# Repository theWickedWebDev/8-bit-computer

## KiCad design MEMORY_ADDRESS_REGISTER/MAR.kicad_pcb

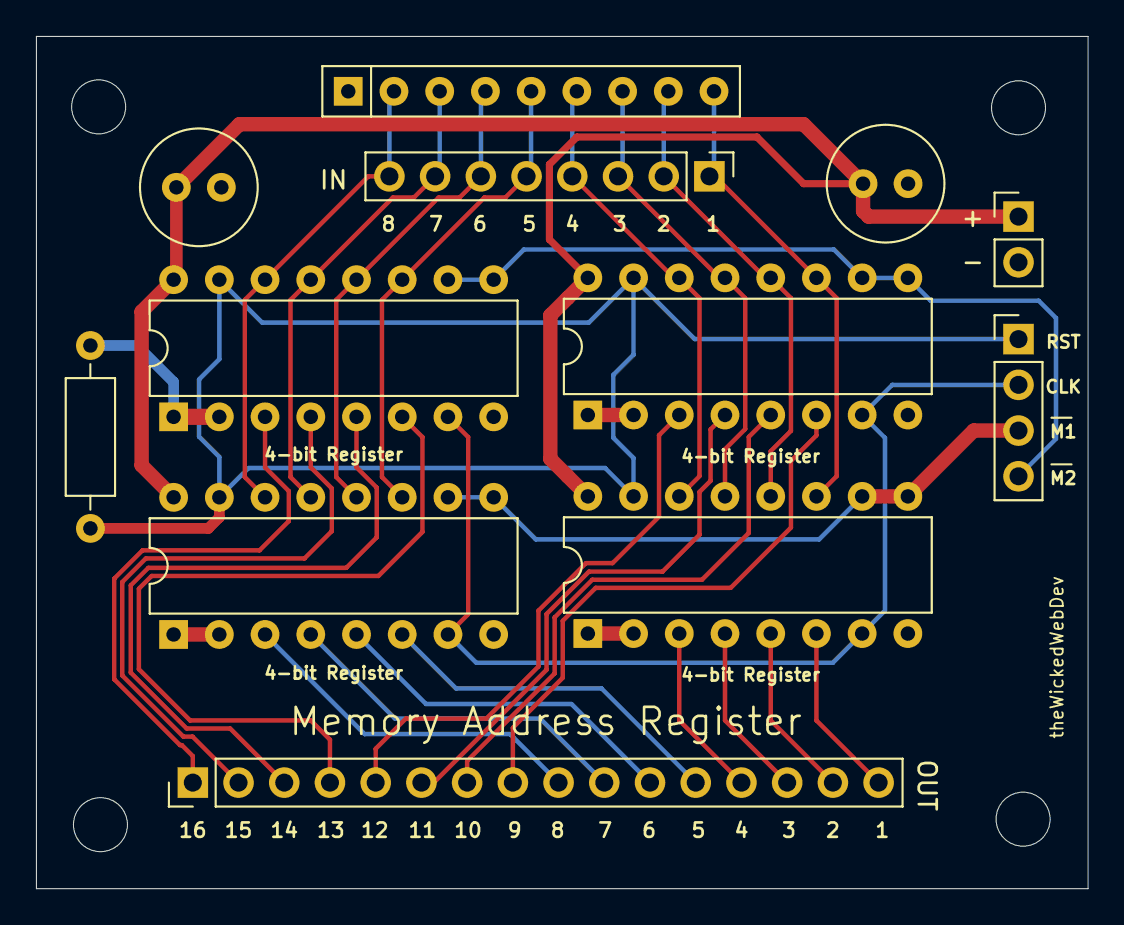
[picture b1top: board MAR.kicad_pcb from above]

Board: 2 copper layers, 58.4 x 47.3 mm, 12 parts (0 on the bottom side), 30 nets.

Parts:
C1, C2: CP1; C_Radial_D6.3mm_H11.0mm_P2.50mm
J1: Conn_01x04; PinHeader_1x02_P2.54mm_Vertical
J2: Conn_01x04; PinHeader_1x04_P2.54mm_Vertical
J3: Conn_01x08; PinHeader_1x08_P2.54mm_Vertical
J4: Conn_01x16; PinHeader_1x16_P2.54mm_Vertical
R1: R_Small_US; R_Axial_DIN0207_L6.3mm_D2.5mm_P10.16mm_Horizontal
RN1: R_Network08_US; R_Array_SIP9
U1, U2, U3, U4: 74LS173; DIP-16_W7.62mm

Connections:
/CLOCK: J2.2, U1.7, U2.7, U3.7, U4.7
/D1: J3.1, RN1.9, U3.11, U4.11
/D2: J3.2, RN1.8, U3.12, U4.12
/D3: J3.3, RN1.7, U3.13, U4.13
/D4: J3.4, RN1.6, U3.14, U4.14
/D5: J3.5, RN1.5, U1.11, U2.11
/D6: J3.6, RN1.4, U1.12, U2.12
/D7: J3.7, RN1.3, U1.13, U2.13
/D8: J3.8, RN1.2, U1.14, U2.14
/MAR1_IN: J2.3, U1.9, U1.10, U3.9, U3.10
/MAR2_IN: J2.4, U2.9, U2.10, U4.9, U4.10
/RESET: J2.1, R1.1, U1.15, U2.15, U3.15, U4.15
/Y1: J4.16, U3.6
/Y2: J4.15, U3.5
/Y3: J4.14, U3.4
/Y4: J4.13, U3.3
/Y5: J4.12, U1.6
/Y6: J4.11, U1.5
/Y7: J4.10, U1.4
/Y8: J4.9, U1.3
/Y9: J4.8, U4.6
/Y10: J4.7, U4.5
/Y11: J4.6, U4.4
/Y12: J4.5, U4.3
/Y13: J4.4, U2.6
/Y14: J4.3, U2.5
/Y15: J4.2, U2.4
/Y16: J4.1, U2.3
GND: C1.2, C2.2, J1.2, R1.2, RN1.1, U1.1, U1.2, U1.8, U2.1, U2.2, U2.8, U3.1, U3.2, U3.8, U4.1, U4.2, U4.8
VCC: C1.1, C2.1, J1.1, U1.16, U2.16, U3.16, U4.16

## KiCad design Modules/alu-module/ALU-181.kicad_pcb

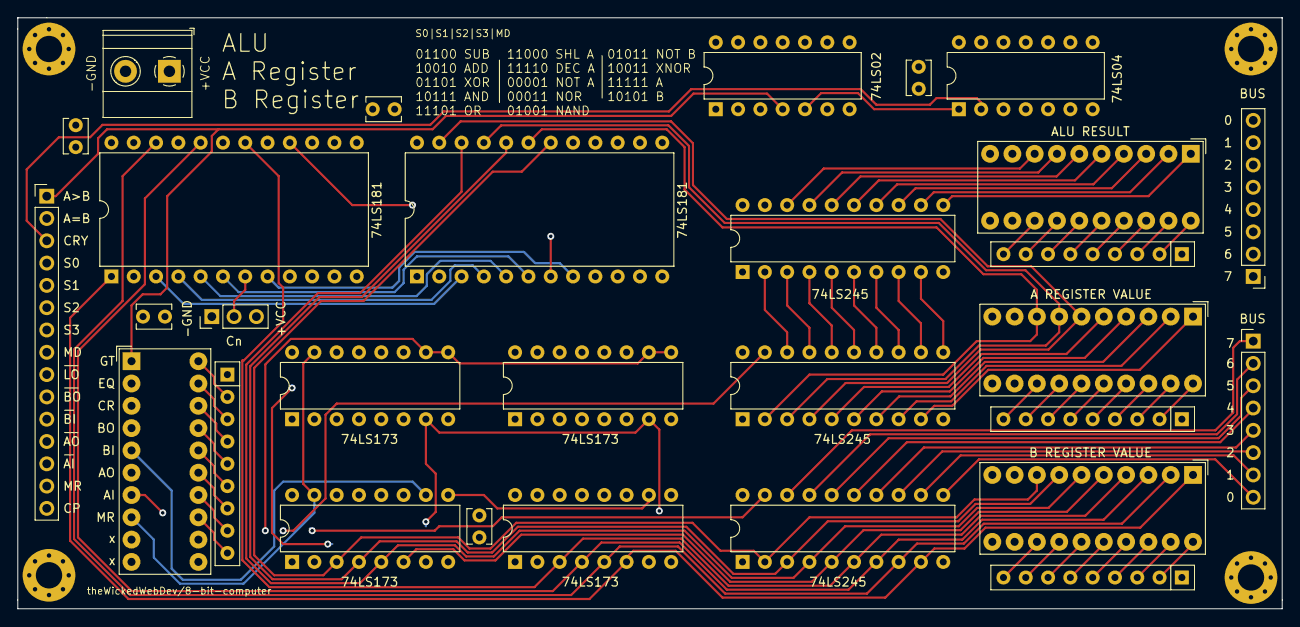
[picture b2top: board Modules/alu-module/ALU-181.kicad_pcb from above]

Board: 4 copper layers, 144.0 x 67.3 mm, 29 parts (0 on the bottom side), 85 nets.

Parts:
BAR1, BAR2, BAR3, BAR4: HDSP-4830_2; HDSP-4830
C1, C2, C3, C4, C5: CP1; C_Disc_D3.8mm_W2.6mm_P2.50mm
J1, J4: Conn_01x08; PinHeader_1x08_P2.54mm_Vertical
J2: Conn_01x15; PinHeader_1x15_P2.54mm_Vertical
J3: Screw_Terminal_01x02; TerminalBlock_Phoenix_MKDS-1,5-2_1x02_P5.00mm_Horizontal
J17: Conn_01x03; PinHeader_1x03_P2.54mm_Vertical
RN1, RN2, RN3, RN4: R_Network08; R_Array_SIP9
U1, U2, U10: 74LS245; DIP-20_W7.62mm
U3, U4, U5, U6: 74LS173; DIP-16_W7.62mm
U7: 74LS04; DIP-14_W7.62mm
U8: 74LS02; DIP-14_W7.62mm
U9, U11: 74LS181; DIP-24_W15.24mm

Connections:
A0: BAR1.1, U1.9, U5.6, U11.2
A1: BAR1.2, U1.8, U5.5, U11.23
A2: BAR1.3, U1.7, U5.4, U11.21
A3: BAR1.4, U1.6, U5.3, U11.19
A4: BAR1.5, U1.5, U3.6, U9.2
A5: BAR1.6, U1.4, U3.5, U9.23
A6: BAR1.7, U1.3, U3.4, U9.21
A7: BAR1.8, U1.2, U3.3, U9.19
ALU_MODE: J2.8, U9.8, U11.8
ALU_OUT: J2.9, U7.3
ALU_S0: J2.4, U9.6, U11.6
ALU_S1: J2.5, U9.5, U11.5
ALU_S2: J2.6, U9.4, U11.4
ALU_S3: J2.7, U9.3, U11.3
A_EQ_B: BAR4.2, J2.2, U8.6, U9.14, U11.14
A_GT_B: BAR4.1, J2.1, U8.4
A_REGISTER_IN: BAR4.7, J2.13, U3.9, U3.10, U5.9, U5.10
A_REGISTER_OUT: BAR4.6, J2.12, U1.19
B0: BAR2.1, U2.9, U6.6, U11.1
B1: BAR2.2, U2.8, U6.5, U11.22
B2: BAR2.3, U2.7, U6.4, U11.20
B3: BAR2.4, U2.6, U6.3, U11.18
B4: BAR2.5, U2.5, U4.6, U9.1
B5: BAR2.6, U2.4, U4.5, U9.22
B6: BAR2.7, U2.3, U4.4, U9.20
B7: BAR2.8, U2.2, U4.3, U9.18
BUS_00: J1.8, J4.8, U1.11, U2.11, U5.11, U6.11, U10.9
BUS_01: J1.7, J4.7, U1.12, U2.12, U5.12, U6.12, U10.8
BUS_02: J1.6, J4.6, U1.13, U2.13, U5.13, U6.13, U10.7
BUS_03: J1.5, J4.5, U1.14, U2.14, U5.14, U6.14, U10.6
BUS_04: J1.4, J4.4, U1.15, U2.15, U3.11, U4.11, U10.5
BUS_05: J1.3, J4.3, U1.16, U2.16, U3.12, U4.12, U10.4
BUS_06: J1.2, J4.2, U1.17, U2.17, U3.13, U4.13, U10.3
BUS_07: J1.1, J4.1, U1.18, U2.18, U3.14, U4.14, U10.2
B_REGISTER_IN: BAR4.5, J2.11, U4.9, U4.10, U6.9, U6.10
B_REGISTER_OUT: BAR4.4, J2.10, U2.19
CARRY: U7.1, U8.5, U9.16
CLOCK: J2.15, U3.7, U4.7, U5.7, U6.7
CN+4: U9.7, U11.16
F0: BAR3.1, U10.11, U11.9
F1: BAR3.2, U10.12, U11.10
F2: BAR3.3, U10.13, U11.11
F3: BAR3.4, U10.14, U11.13
F4: BAR3.5, U9.9, U10.15
F5: BAR3.6, U9.10, U10.16
F6: BAR3.7, U9.11, U10.17
F7: BAR3.8, U9.13, U10.18
GND: C1.2, C2.2, C3.2, C4.2, C5.2, J3.2, J17.1, RN1.1, RN2.1, RN3.1, RN4.1, U1.10, U2.10, U3.1, U3.2, U3.8, U4.1, U4.2, U4.8, U5.1, U5.2, U5.8, U6.1, U6.2, U6.8, U7.7, U8.7, U9.12, U10.1, U10.10, U11.12
NOT_ALU_OUT: U7.4, U10.19
NOT_CARRY: BAR4.3, J2.3, U7.2
unnamed: BAR1.13, RN1.9
unnamed: BAR1.14, RN1.8
unnamed: BAR1.15, RN1.7
unnamed: BAR1.16, RN1.6
unnamed: BAR1.17, RN1.5
unnamed: BAR1.18, RN1.4
unnamed: BAR1.19, RN1.3
unnamed: BAR1.20, RN1.2
unnamed: BAR2.13, RN2.9
unnamed: BAR2.14, RN2.8
unnamed: BAR2.15, RN2.7
unnamed: BAR2.16, RN2.6
unnamed: BAR2.17, RN2.5
unnamed: BAR2.18, RN2.4
unnamed: BAR2.19, RN2.3
unnamed: BAR2.20, RN2.2
unnamed: BAR3.13, RN3.9
unnamed: BAR3.14, RN3.8
unnamed: BAR3.15, RN3.7
unnamed: BAR3.16, RN3.6
unnamed: BAR3.17, RN3.5
unnamed: BAR3.18, RN3.4
unnamed: BAR3.19, RN3.3
unnamed: BAR3.20, RN3.2
unnamed: BAR4.13, RN4.9
unnamed: BAR4.14, RN4.8
unnamed: BAR4.15, RN4.7
unnamed: BAR4.16, RN4.6
unnamed: BAR4.17, RN4.5
unnamed: BAR4.18, RN4.4
unnamed: BAR4.19, RN4.3
unnamed: BAR4.20, RN4.2
unnamed: J17.2, U11.7
RESET: BAR4.8, J2.14, U3.15, U4.15, U5.15, U6.15
VCC: C1.1, C2.1, C3.1, C4.1, C5.1, J3.1, J17.3, U1.1, U1.20, U2.1, U2.20, U3.16, U4.16, U5.16, U6.16, U7.14, U8.14, U9.24, U10.20, U11.24

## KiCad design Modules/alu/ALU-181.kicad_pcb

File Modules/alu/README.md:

# ALU with 74LS181

<br/>

<br/>

<br/>

<br/>

<br/>

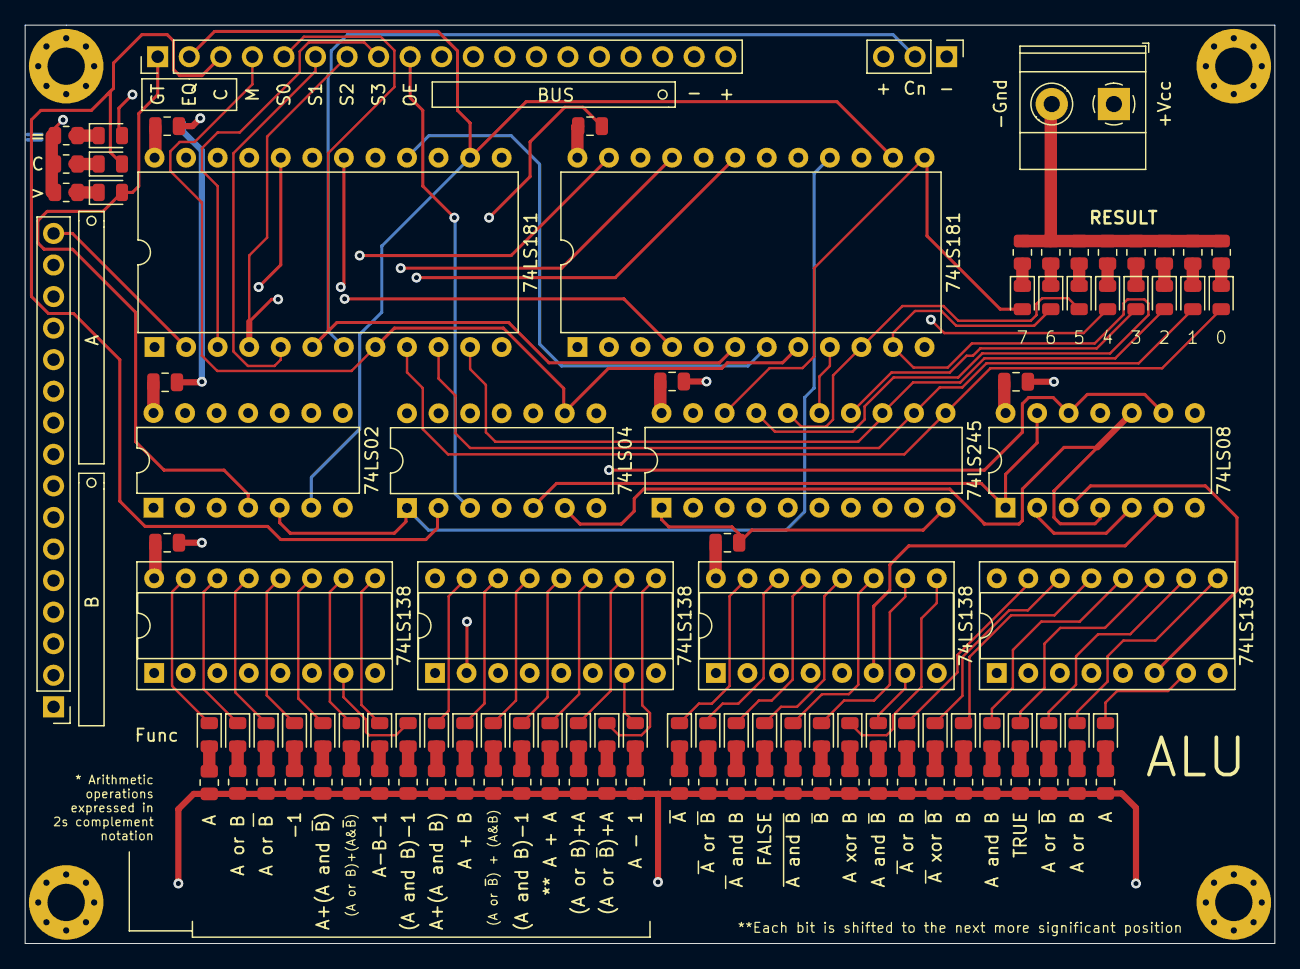
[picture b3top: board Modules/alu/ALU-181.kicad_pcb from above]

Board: 4 copper layers, 100.6 x 73.9 mm, 107 parts (0 on the bottom side), 128 nets.

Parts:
C1, C2, C3, C4, C5, C6, C7: CP1; C_0805_2012Metric
D1, D2, D3, D4, D5, D6, D7, D8, D9, D10, D11, D12, D13, D14, D15, D16, D17, D18, D19, D20, D21, D22, D23, D24, D25, D26, D27, D28, D29, D30, D31, D32, D33, D34, D35, D36, D37, D38, D39, D40, D41, D42, D43: LED; LED_0805_2012Metric
J2: Conn_01x19; PinHeader_1x19_P2.54mm_Vertical
J3: Screw_Terminal_01x02; TerminalBlock_Phoenix_MKDS-1,5-2_1x02_P5.00mm_Horizontal
J4: Conn_01x16; PinHeader_1x16_P2.54mm_Vertical
J17: Conn_01x03; PinHeader_1x03_P2.54mm_Vertical
R1, R2, R3, R4, R5, R6, R7, R8, R9, R10, R11, R12, R13, R14, R15, R16, R17, R18, R19, R20, R21, R22, R23, R24, R25, R26, R27, R28, R29, R30, R31, R32, R33, R34, R35, R36, R37, R38, R39, R40, R41, R42, R43: R_Small_US; R_0805_2012Metric
U1, U2, U4, U5: 74LS138; DIP-16_W7.62mm_Socket
U3: 74LS08; DIP-14_W7.62mm
U7: 74LS04; DIP-14_W7.62mm
U8: 74LS02; DIP-14_W7.62mm
U9, U11: 74LS181; DIP-24_W15.24mm
U10: 74LS245; DIP-20_W7.62mm

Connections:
!ALU_MODE: U3.9, U3.12, U7.8
!ALU_S3: U3.4, U3.10, U7.6
A0: J4.16, U11.2
A1: J4.15, U11.23
A2: J4.14, U11.21
A3: J4.13, U11.19
A4: J4.12, U9.2
A5: J4.11, U9.23
A6: J4.10, U9.21
A7: J4.9, U9.19
ALU_MODE: J2.4, U3.2, U3.5, U7.9, U9.8, U11.8
ALU_OUT: J2.9, U7.3
ALU_S0: J2.5, U1.1, U2.1, U4.1, U5.1, U9.6, U11.6
ALU_S1: J2.6, U1.2, U2.2, U4.2, U5.2, U9.5, U11.5
ALU_S2: J2.7, U1.3, U2.3, U4.3, U5.3, U9.4, U11.4
ALU_S3: J2.8, U3.1, U3.13, U7.5, U9.3, U11.3
A_EQ_B: D42.2, J2.2, U8.6, U9.14, U11.14
A_GT_B: D43.2, J2.1, U8.4
B0: J4.8, U11.1
B1: J4.7, U11.22
B2: J4.6, U11.20
B3: J4.5, U11.18
B4: J4.4, U9.1
B5: J4.3, U9.22
B6: J4.2, U9.20
B7: J4.1, U9.18
BUS_00: J2.17, U10.9
BUS_01: J2.16, U10.8
BUS_02: J2.15, U10.7
BUS_03: J2.14, U10.6
BUS_04: J2.13, U10.5
BUS_05: J2.12, U10.4
BUS_06: J2.11, U10.3
BUS_07: J2.10, U10.2
CARRY: U7.1, U8.5, U9.16
CN+4: U9.7, U11.16
F0: D8.2, U10.11, U11.9
F1: D7.2, U10.12, U11.10
F2: D6.2, U10.13, U11.11
F3: D5.2, U10.14, U11.13
F4: D4.2, U9.9, U10.15
F5: D3.2, U9.10, U10.16
F6: D2.2, U9.11, U10.17
F7: D1.2, U9.13, U10.18
GND: C1.2, C2.2, C3.2, C4.2, C5.2, C6.2, C7.2, J2.18, J3.2, J17.1, R1.2, R2.2, R3.2, R4.2, R5.2, R6.2, R7.2, R8.2, R41.2, R42.2, R43.2, U1.4, U1.5, U1.8, U2.4, U2.5, U2.8, U3.7, U4.4, U4.5, U4.8, U5.4, U5.5, U5.8, U7.7, U8.7, U9.12, U10.1, U10.10, U11.12
NOT_ALU_OUT: U7.4, U10.19
NOT_CARRY: D41.2, J2.3, U7.2
unnamed: D1.1, R1.1
unnamed: D2.1, R2.1
unnamed: D3.1, R3.1
unnamed: D4.1, R4.1
unnamed: D5.1, R5.1
unnamed: D6.1, R6.1
unnamed: D7.1, R7.1
unnamed: D8.1, R8.1
unnamed: D9.1, U1.7
unnamed: D9.2, R16.1
unnamed: D10.1, U1.9
unnamed: D10.2, R15.1
unnamed: D11.1, U1.10
unnamed: D11.2, R14.1
unnamed: D12.1, U1.11
unnamed: D12.2, R13.1
unnamed: D13.1, U1.12
unnamed: D13.2, R12.1
unnamed: D14.1, U1.13
unnamed: D14.2, R11.1
unnamed: D15.1, U1.14
unnamed: D15.2, R10.1
unnamed: D16.1, U1.15
unnamed: D16.2, R9.1
unnamed: D17.1, U2.7
unnamed: D17.2, R24.1
unnamed: D18.1, U2.9
unnamed: D18.2, R23.1
unnamed: D19.1, U2.10
unnamed: D19.2, R22.1
unnamed: D20.1, U2.11
unnamed: D20.2, R21.1
unnamed: D21.1, U2.12
unnamed: D21.2, R20.1
unnamed: D22.1, U2.13
unnamed: D22.2, R19.1
unnamed: D23.1, U2.14
unnamed: D23.2, R18.1
unnamed: D24.1, U2.15
unnamed: D24.2, R17.1
unnamed: D25.1, U4.7
unnamed: D25.2, R32.1
unnamed: D26.1, U4.9
unnamed: D26.2, R31.1
unnamed: D27.1, U4.10
unnamed: D27.2, R30.1
unnamed: D28.1, U4.11
unnamed: D28.2, R29.1
unnamed: D29.1, U4.12
unnamed: D29.2, R28.1
unnamed: D30.1, U4.13
unnamed: D30.2, R27.1
unnamed: D31.1, U4.14
unnamed: D31.2, R26.1
unnamed: D32.1, U4.15
unnamed: D32.2, R25.1
unnamed: D33.1, U5.7
unnamed: D33.2, R40.1
unnamed: D34.1, U5.9
unnamed: D34.2, R39.1
unnamed: D35.1, U5.10
unnamed: D35.2, R38.1
unnamed: D36.1, U5.11
unnamed: D36.2, R37.1
unnamed: D37.1, U5.12
unnamed: D37.2, R36.1
unnamed: D38.1, U5.13
unnamed: D38.2, R35.1
unnamed: D39.1, U5.14
unnamed: D39.2, R34.1
unnamed: D40.1, U5.15
unnamed: D40.2, R33.1
unnamed: D41.1, R41.1
unnamed: D42.1, R42.1
unnamed: D43.1, R43.1
unnamed: J17.2, U11.7
unnamed: U1.6, U3.8
unnamed: U2.6, U3.11
unnamed: U3.3, U5.6
unnamed: U3.6, U4.6
VCC: C1.1, C2.1, C3.1, C4.1, C5.1, C6.1, C7.1, J2.19, J3.1, J17.3, R9.2, R10.2, R11.2, R12.2, R13.2, R14.2, R15.2, R16.2, R17.2, R18.2, R19.2, R20.2, R21.2, R22.2, R23.2, R24.2, R25.2, R26.2, R27.2, R28.2, R29.2, R30.2, R31.2, R32.2, R33.2, R34.2, R35.2, R36.2, R37.2, R38.2, R39.2, R40.2, U1.16, U2.16, U3.14, U4.16, U5.16, U7.14, U8.14, U9.24, U10.20, U11.24

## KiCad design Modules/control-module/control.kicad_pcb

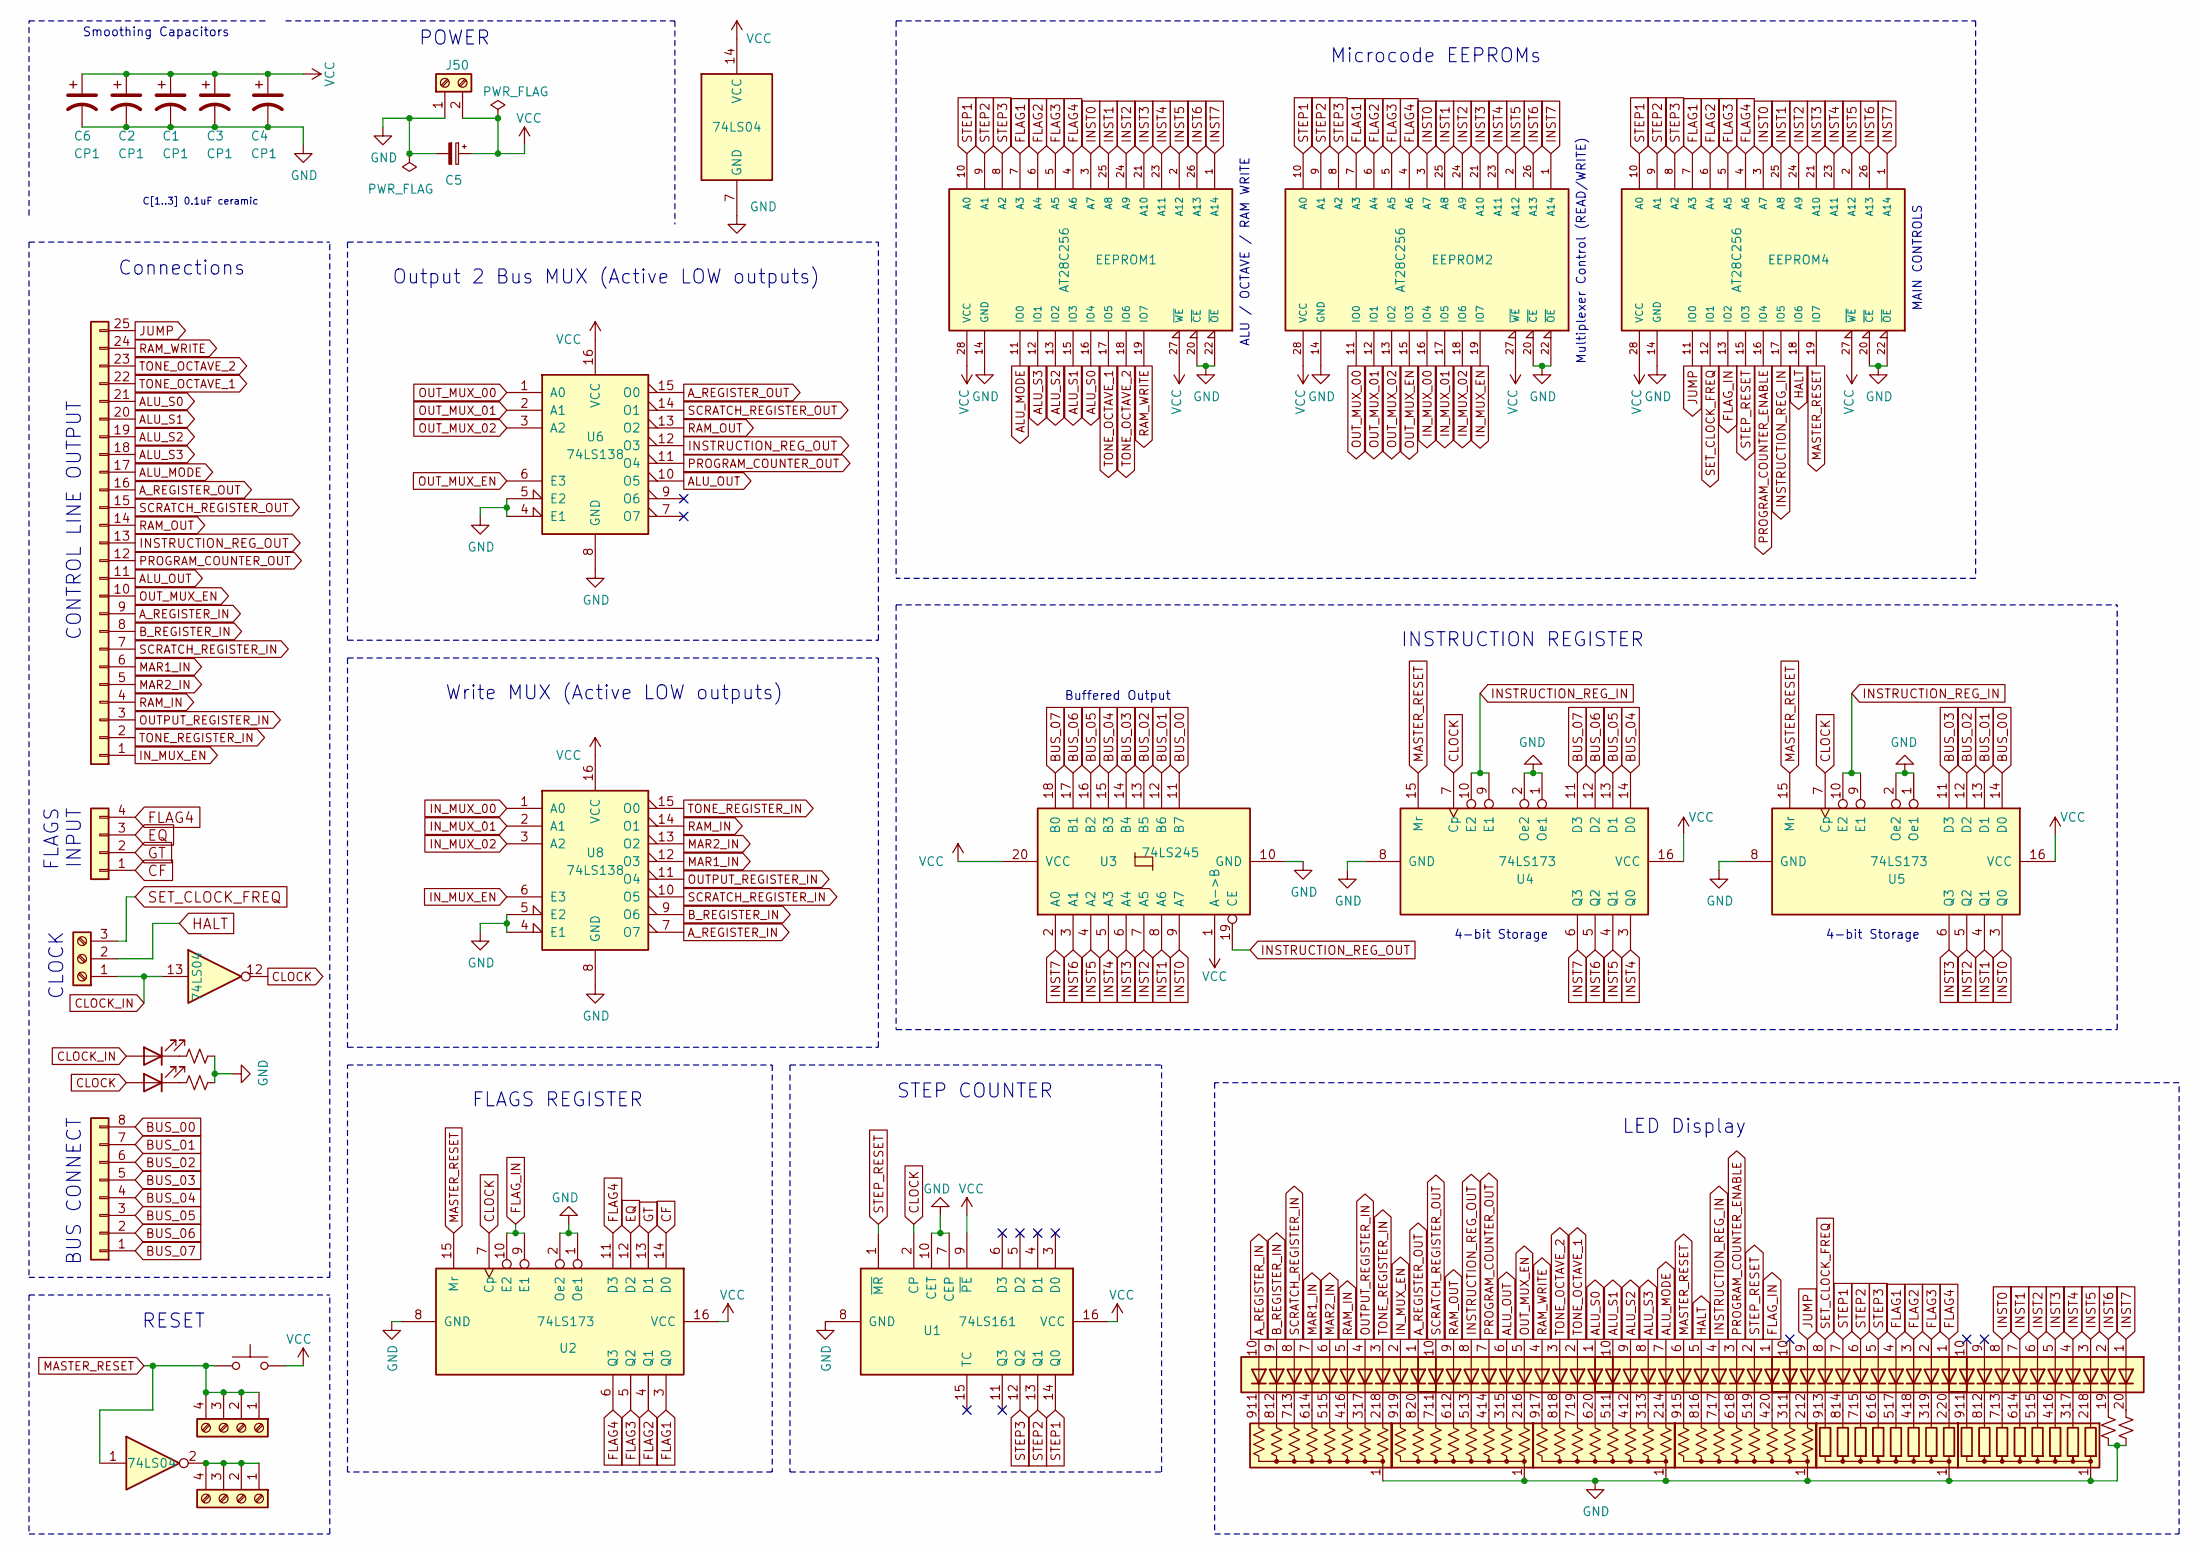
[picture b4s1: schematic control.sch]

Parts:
BAR1, BAR2, BAR3, BAR4, BAR5: HDSP-4850_2; HDSP-4850
C1, C2, C3, C4, C6: CP1; C_Disc_D3.8mm_W2.6mm_P2.50mm
C5: CP_Small; CP_Radial_D8.0mm_P3.80mm
D1, D2: LED; LED_D3.0mm
EEPROM1, EEPROM2, EEPROM4: AT28C256; DIP_Socket-40_W11.9_W12.7_W15.24_W17.78_W18.5_3M_240-1280-0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
J2, J4: Screw_Terminal_01x04; TerminalBlock_Phoenix_MKDS-1,5-4_1x04_P5.00mm_Horizontal
J3: Conn_01x25; PinHeader_1x25_P2.54mm_Vertical
J5: Conn_01x03; TerminalBlock_Phoenix_MKDS-1,5-3_1x03_P5.00mm_Horizontal
J8: Conn_01x08; PinHeader_1x08_P2.54mm_Vertical
J12: Conn_01x04; PinHeader_1x04_P2.54mm_Vertical
J50: Screw_Terminal_01x02; TerminalBlock_Phoenix_MKDS-1,5-2_1x02_P5.00mm_Horizontal
R1, R2, R3, R4: R_Small_US; R_Axial_DIN0207_L6.3mm_D2.5mm_P10.16mm_Horizontal
RN1, RN2: R_Network08; R_Array_SIP9
RN14, RN15, RN16, RN17: R_Network08_US; R_Array_SIP9
SW6: SW_Push; SW_PUSH_6mm
U1: 74LS161; DIP-16_W7.62mm
U2, U4, U5: 74LS173; DIP-16_W7.62mm
U3: 74LS245; DIP-20_W7.62mm
U6, U8: 74LS138; DIP-16_W7.62mm
U7: 74LS04; DIP-14_W7.62mm

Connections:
ALU_MODE: BAR3.7 (A), EEPROM1.11 (IO0), J3.17
ALU_OUT: BAR2.6 (A), J3.11, U6.10 (O5)
ALU_S0: BAR2.1 (A), EEPROM1.16 (IO4), J3.21
ALU_S1: BAR3.10 (A), EEPROM1.15 (IO3), J3.20
ALU_S2: BAR3.9 (A), EEPROM1.13 (IO2), J3.19
ALU_S3: BAR3.8 (A), EEPROM1.12 (IO1), J3.18
A_REGISTER_IN: BAR1.10 (A), J3.9, U8.7 (O7)
A_REGISTER_OUT: BAR1.1 (A), J3.16, U6.15 (O0)
BUS_00: J8.8, U3.11 (B7), U5.14 (D0)
BUS_01: J8.7, U3.12 (B6), U5.13 (D1)
BUS_02: J8.6, U3.13 (B5), U5.12 (D2)
BUS_03: J8.5, U3.14 (B4), U5.11 (D3)
BUS_04: J8.4, U3.15 (B3), U4.14 (D0)
BUS_05: J8.3, U3.16 (B2), U4.13 (D1)
BUS_06: J8.2, U3.17 (B1), U4.12 (D2)
BUS_07: J8.1, U3.18 (B0), U4.11 (D3)
B_REGISTER_IN: BAR1.9 (A), J3.8, U8.9 (O6)
CF: J12.1, U2.14 (D0)
CLOCK: D2.2 (A), U1.2 (CP), U2.7 (Cp), U4.7 (Cp), U5.7 (Cp), U7.12
CLOCK_IN: D1.2 (A), J5.1, U7.13
EQ: J12.3, U2.12 (D2)
FLAG1: BAR4.4 (A), EEPROM1.7 (A3), EEPROM2.7 (A3), EEPROM4.7 (A3), U2.3 (Q0)
FLAG2: BAR4.3 (A), EEPROM1.6 (A4), EEPROM2.6 (A4), EEPROM4.6 (A4), U2.4 (Q1)
FLAG3: BAR4.2 (A), EEPROM1.5 (A5), EEPROM2.5 (A5), EEPROM4.5 (A5), U2.5 (Q2)
FLAG4: BAR4.1 (A), EEPROM1.4 (A6), EEPROM2.4 (A6), EEPROM4.4 (A6), J12.4, U2.6 (Q3), U2.11 (D3)
FLAG_IN: BAR3.1 (A), EEPROM4.13 (IO2), U2.9 (E1), U2.10 (E2)
GND: C1.2, C2.2, C3.2, C4.2, C5.2, C6.2, EEPROM1.14 (GND), EEPROM1.20 (~CE), EEPROM1.22 (~OE), EEPROM2.14 (GND), EEPROM2.20 (~CE), EEPROM2.22 (~OE), EEPROM4.14 (GND), EEPROM4.20 (~CE), EEPROM4.22 (~OE), J50.1, R1.2, R2.2, R3.1, R4.1, RN1.1 (common), RN2.1 (common), RN14.1 (common), RN15.1 (common), RN16.1 (common), RN17.1 (common), U1.7 (CEP), U1.8 (GND), U1.10 (CET), U2.1 (Oe1), U2.2 (Oe2), U2.8 (GND), U3.10 (GND), U4.1 (Oe1), U4.2 (Oe2), U4.8 (GND), U5.1 (Oe1), U5.2 (Oe2), U5.8 (GND), U6.4 (E1), U6.5 (E2), U6.8 (GND), U7.7 (GND), U8.4 (E1), U8.5 (E2), U8.8 (GND)
GT: J12.2, U2.13 (D1)
HALT: BAR3.5 (A), EEPROM4.18 (IO6), J5.2
INST0: BAR5.8 (A), EEPROM1.3 (A7), EEPROM2.3 (A7), EEPROM4.3 (A7), U3.9 (A7), U5.3 (Q0)
INST1: BAR5.7 (A), EEPROM1.25 (A8), EEPROM2.25 (A8), EEPROM4.25 (A8), U3.8 (A6), U5.4 (Q1)
INST2: BAR5.6 (A), EEPROM1.24 (A9), EEPROM2.24 (A9), EEPROM4.24 (A9), U3.7 (A5), U5.5 (Q2)
INST3: BAR5.5 (A), EEPROM1.21 (A10), EEPROM2.21 (A10), EEPROM4.21 (A10), U3.6 (A4), U5.6 (Q3)
INST4: BAR5.4 (A), EEPROM1.23 (A11), EEPROM2.23 (A11), EEPROM4.23 (A11), U3.5 (A3), U4.3 (Q0)
INST5: BAR5.3 (A), EEPROM1.2 (A12), EEPROM2.2 (A12), EEPROM4.2 (A12), U3.4 (A2), U4.4 (Q1)
INST6: BAR5.2 (A), EEPROM1.26 (A13), EEPROM2.26 (A13), EEPROM4.26 (A13), U3.3 (A1), U4.5 (Q2)
INST7: BAR5.1 (A), EEPROM1.1 (A14), EEPROM2.1 (A14), EEPROM4.1 (A14), U3.2 (A0), U4.6 (Q3)
INSTRUCTION_REG_IN: BAR3.4 (A), EEPROM4.17 (IO5), U4.9 (E1), U4.10 (E2), U5.9 (E1), U5.10 (E2)
INSTRUCTION_REG_OUT: BAR2.8 (A), J3.13, U3.19 (CE), U6.12 (O3)
IN_MUX_00: EEPROM2.16 (IO4), U8.1 (A0)
IN_MUX_01: EEPROM2.17 (IO5), U8.2 (A1)
IN_MUX_02: EEPROM2.18 (IO6), U8.3 (A2)
IN_MUX_EN: BAR1.2 (A), EEPROM2.19 (IO7), J3.1, U8.6 (E3)
JUMP: BAR4.9 (A), EEPROM4.11 (IO0), J3.25
MAR1_IN: BAR1.7 (A), J3.6, U8.12 (O3)
MAR2_IN: BAR1.6 (A), J3.5, U8.13 (O2)
MASTER_RESET: BAR3.6 (A), EEPROM4.19 (IO7), J2.1, J2.2, J2.3, J2.4, SW6.1, U2.15 (Mr), U4.15 (Mr), U5.15 (Mr), U7.1
unnamed: BAR1.11 (K), RN14.9 (R8)
unnamed: BAR1.12 (K), RN14.8 (R7)
unnamed: BAR1.13 (K), RN14.7 (R6)
unnamed: BAR1.14 (K), RN14.6 (R5)
unnamed: BAR1.15 (K), RN14.5 (R4)
unnamed: BAR1.16 (K), RN14.4 (R3)
unnamed: BAR1.17 (K), RN14.3 (R2)
unnamed: BAR1.18 (K), RN14.2 (R1)
unnamed: BAR1.19 (K), RN15.9 (R8)
unnamed: BAR1.20 (K), RN15.8 (R7)
unnamed: BAR2.11 (K), RN15.7 (R6)
unnamed: BAR2.12 (K), RN15.6 (R5)
unnamed: BAR2.13 (K), RN15.5 (R4)
unnamed: BAR2.14 (K), RN15.4 (R3)
unnamed: BAR2.15 (K), RN15.3 (R2)
unnamed: BAR2.16 (K), RN15.2 (R1)
unnamed: BAR2.17 (K), RN16.9 (R8)
unnamed: BAR2.18 (K), RN16.8 (R7)
unnamed: BAR2.19 (K), RN16.7 (R6)
unnamed: BAR2.20 (K), RN16.6 (R5)
unnamed: BAR3.11 (K), RN16.5 (R4)
unnamed: BAR3.12 (K), RN16.4 (R3)
unnamed: BAR3.13 (K), RN16.3 (R2)
unnamed: BAR3.14 (K), RN16.2 (R1)
unnamed: BAR3.15 (K), RN17.9 (R8)
unnamed: BAR3.16 (K), RN17.8 (R7)
unnamed: BAR3.17 (K), RN17.7 (R6)
unnamed: BAR3.18 (K), RN17.6 (R5)
unnamed: BAR3.19 (K), RN17.5 (R4)
unnamed: BAR3.20 (K), RN17.4 (R3)
unnamed: BAR4.11 (K), RN17.3 (R2)
unnamed: BAR4.12 (K), RN17.2 (R1)
unnamed: BAR4.13 (K), RN1.9 (R8)
unnamed: BAR4.14 (K), RN1.8 (R7)
unnamed: BAR4.15 (K), RN1.7 (R6)
unnamed: BAR4.16 (K), RN1.6 (R5)
unnamed: BAR4.17 (K), RN1.5 (R4)
unnamed: BAR4.18 (K), RN1.4 (R3)
unnamed: BAR4.19 (K), RN1.3 (R2)
unnamed: BAR4.20 (K), RN1.2 (R1)
unnamed: BAR5.11 (K), RN2.9 (R8)
unnamed: BAR5.12 (K), RN2.8 (R7)
unnamed: BAR5.13 (K), RN2.7 (R6)
unnamed: BAR5.14 (K), RN2.6 (R5)
unnamed: BAR5.15 (K), RN2.5 (R4)
unnamed: BAR5.16 (K), RN2.4 (R3)
unnamed: BAR5.17 (K), RN2.3 (R2)
unnamed: BAR5.18 (K), RN2.2 (R1)
unnamed: BAR5.19 (K), R1.1
unnamed: BAR5.20 (K), R2.1
unnamed: D1.1 (K), R3.2
unnamed: D2.1 (K), R4.2
unnamed: J4.1, J4.2, J4.3, J4.4, U7.2
OUTPUT_REGISTER_IN: BAR1.4 (A), J3.3, U8.11 (O4)
OUT_MUX_00: EEPROM2.11 (IO0), U6.1 (A0)
OUT_MUX_01: EEPROM2.12 (IO1), U6.2 (A1)
OUT_MUX_02: EEPROM2.13 (IO2), U6.3 (A2)
OUT_MUX_EN: BAR2.5 (A), EEPROM2.15 (IO3), J3.10, U6.6 (E3)
PROGRAM_COUNTER_ENABLE: BAR3.3 (A), EEPROM4.16 (IO4)
PROGRAM_COUNTER_OUT: BAR2.7 (A), J3.12, U6.11 (O4)
RAM_IN: BAR1.5 (A), J3.4, U8.14 (O1)
RAM_OUT: BAR2.9 (A), J3.14, U6.13 (O2)
RAM_WRITE: BAR2.4 (A), EEPROM1.19 (IO7), J3.24
SCRATCH_REGISTER_IN: BAR1.8 (A), J3.7, U8.10 (O5)
SCRATCH_REGISTER_OUT: BAR2.10 (A), J3.15, U6.14 (O1)
SET_CLOCK_FREQ: BAR4.8 (A), EEPROM4.12 (IO1), J5.3
STEP1: BAR4.7 (A), EEPROM1.10 (A0), EEPROM2.10 (A0), EEPROM4.10 (A0), U1.14 (Q0)
STEP2: BAR4.6 (A), EEPROM1.9 (A1), EEPROM2.9 (A1), EEPROM4.9 (A1), U1.13 (Q1)
STEP3: BAR4.5 (A), EEPROM1.8 (A2), EEPROM2.8 (A2), EEPROM4.8 (A2), U1.12 (Q2)
STEP_RESET: BAR3.2 (A), EEPROM4.15 (IO3), U1.1 (~MR)
TONE_OCTAVE_1: BAR2.2 (A), EEPROM1.17 (IO5), J3.22
TONE_OCTAVE_2: BAR2.3 (A), EEPROM1.18 (IO6), J3.23
TONE_REGISTER_IN: BAR1.3 (A), J3.2, U8.15 (O0)
VCC: C1.1, C2.1, C3.1, C4.1, C5.1, C6.1, EEPROM1.27 (~WE), EEPROM1.28 (VCC), EEPROM2.27 (~WE), EEPROM2.28 (VCC), EEPROM4.27 (~WE), EEPROM4.28 (VCC), J50.2, SW6.2, U1.9 (~PE), U1.16 (VCC), U2.16 (VCC), U3.1 (A->B), U3.20 (VCC), U4.16 (VCC), U5.16 (VCC), U6.16 (VCC), U7.14 (VCC), U8.16 (VCC)

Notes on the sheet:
POWER
RESET
LED Display
Connections
Microcode EEPROMs
Smoothing Capacitors
BUS CONNECT
C[1..3] 0.1uF ceramic
INSTRUCTION REGISTER
4-bit Storage
Buffered Output
FLAGS REGISTER
STEP COUNTER
Write MUX (Active LOW outputs)
Output 2 Bus MUX (Active LOW outputs)
ALU / OCTAVE / RAM WRITE
Multiplexer Control (READ/WRITE)
MAIN CONTROLS
CLOCK
FLAGS INPUT
CONTROL LINE OUTPUT

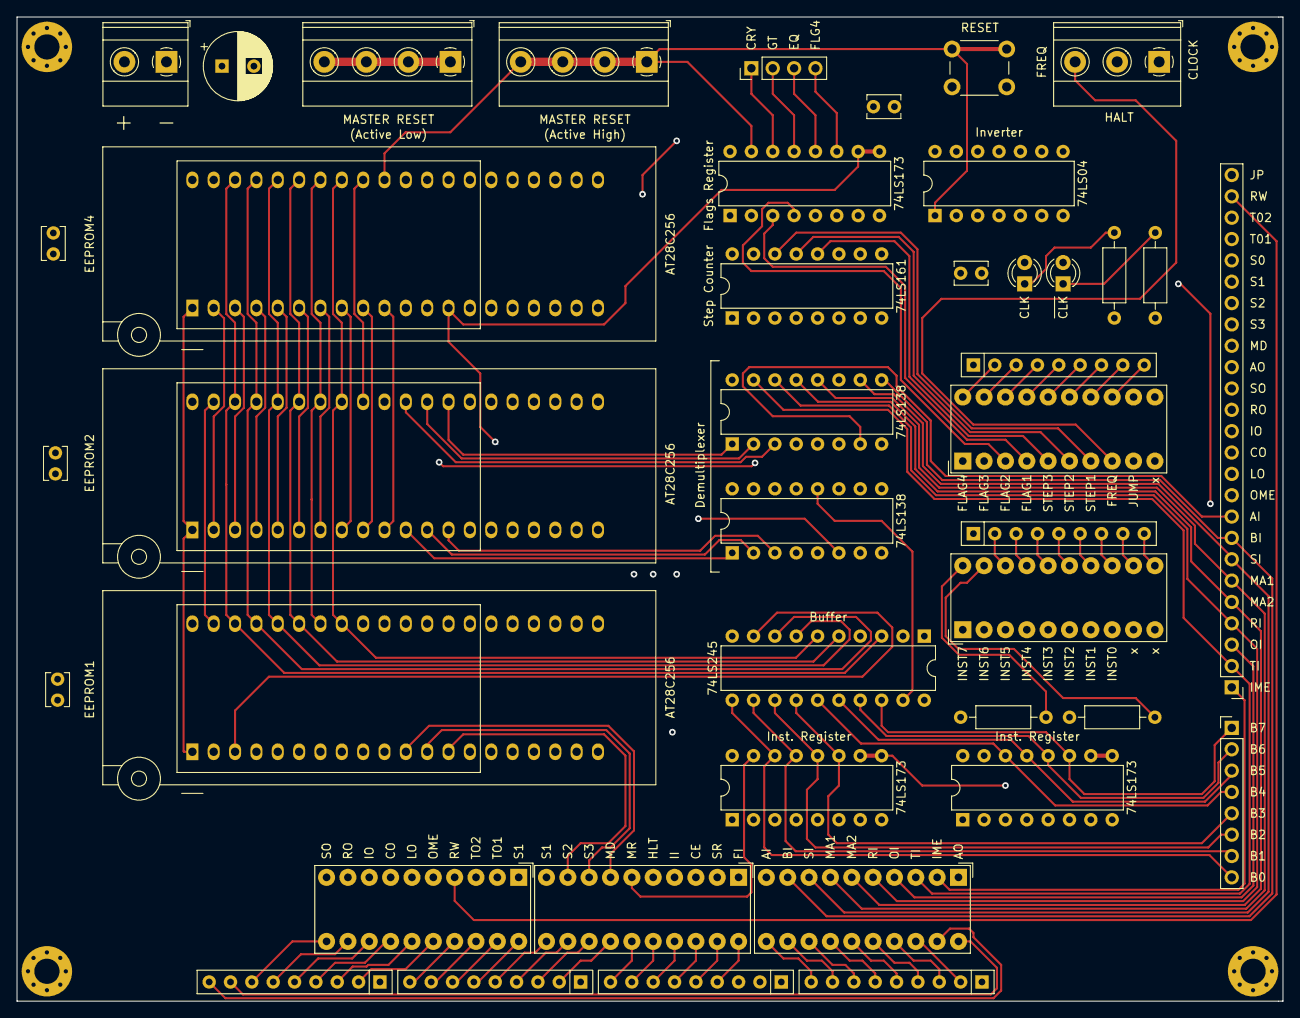
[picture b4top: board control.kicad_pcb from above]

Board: 4 copper layers, 150.6 x 117.1 mm, 42 parts (0 on the bottom side), 121 nets.

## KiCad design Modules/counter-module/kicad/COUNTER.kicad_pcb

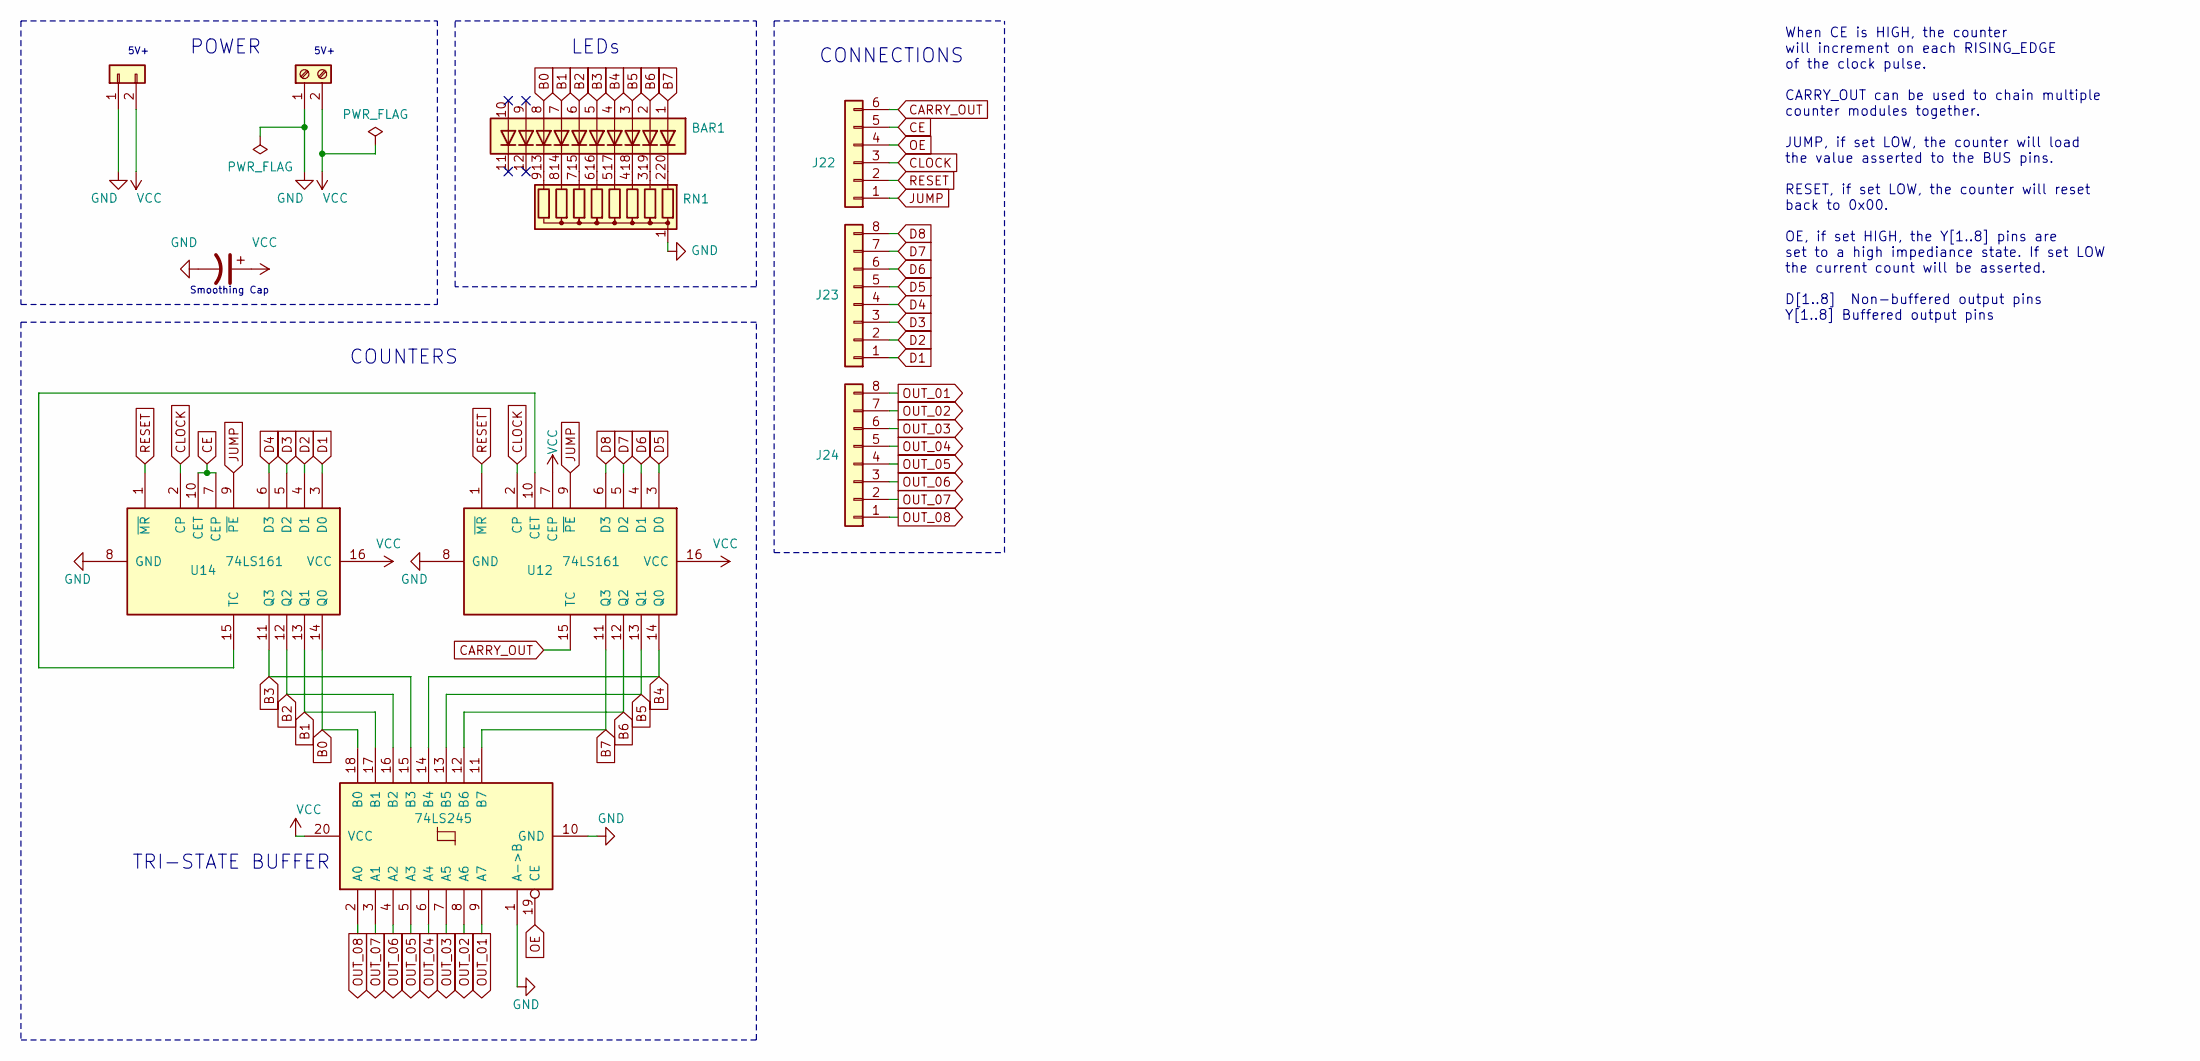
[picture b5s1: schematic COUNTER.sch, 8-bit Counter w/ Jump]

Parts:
BAR1: HDSP-4830_2; HDSP-4830
C8: CP1; C_Radial_D6.3mm_H11.0mm_P2.50mm
J1: Screw_Terminal_01x02; TerminalBlock_Phoenix_MKDS-1,5-2_1x02_P5.00mm_Horizontal
J10: Conn_01x04; PinHeader_1x02_P2.54mm_Vertical
J22: Conn_01x06; PinHeader_1x06_P2.54mm_Vertical
J23, J24: Conn_01x08; PinHeader_1x08_P2.54mm_Vertical
RN1: R_Network08; R_Array_SIP9
U12, U14: 74LS161; DIP-16_W7.62mm
U47: 74LS245; DIP-20_W7.62mm

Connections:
B0: BAR1.8 (A), U14.14 (Q0), U47.18 (B0)
B1: BAR1.7 (A), U14.13 (Q1), U47.17 (B1)
B2: BAR1.6 (A), U14.12 (Q2), U47.16 (B2)
B3: BAR1.5 (A), U14.11 (Q3), U47.15 (B3)
B4: BAR1.4 (A), U12.14 (Q0), U47.14 (B4)
B5: BAR1.3 (A), U12.13 (Q1), U47.13 (B5)
B6: BAR1.2 (A), U12.12 (Q2), U47.12 (B6)
B7: BAR1.1 (A), U12.11 (Q3), U47.11 (B7)
CARRY_OUT: J22.6, U12.15 (TC)
CE: J22.5, U14.7 (CEP), U14.10 (CET)
CLOCK: J22.3, U12.2 (CP), U14.2 (CP)
D1: J23.1, U14.3 (D0)
D2: J23.2, U14.4 (D1)
D3: J23.3, U14.5 (D2)
D4: J23.4, U14.6 (D3)
D5: J23.5, U12.3 (D0)
D6: J23.6, U12.4 (D1)
D7: J23.7, U12.5 (D2)
D8: J23.8, U12.6 (D3)
GND: J1.1, J10.1, RN1.1 (common), U12.8 (GND), U14.8 (GND), U47.1 (A->B), U47.10 (GND); also elsewhere on the board
JUMP: J22.1, U12.9 (~PE), U14.9 (~PE)
unnamed: BAR1.13 (K), RN1.9 (R8)
unnamed: BAR1.14 (K), RN1.8 (R7)
unnamed: BAR1.15 (K), RN1.7 (R6)
unnamed: BAR1.16 (K), RN1.6 (R5)
unnamed: BAR1.17 (K), RN1.5 (R4)
unnamed: BAR1.18 (K), RN1.4 (R3)
unnamed: BAR1.19 (K), RN1.3 (R2)
unnamed: BAR1.20 (K), RN1.2 (R1)
unnamed: U12.10 (CET), U14.15 (TC)
OE: J22.4, U47.19 (CE)
OUT_01: J24.8, U47.9 (A7)
OUT_02: J24.7, U47.8 (A6)
OUT_03: J24.6, U47.7 (A5)
OUT_04: J24.5, U47.6 (A4)
OUT_05: J24.4, U47.5 (A3)
OUT_06: J24.3, U47.4 (A2)
OUT_07: J24.2, U47.3 (A1)
OUT_08: J24.1, U47.2 (A0)
RESET: J22.2, U12.1 (~MR), U14.1 (~MR)
VCC: J1.2, J10.2, U12.7 (CEP), U12.16 (VCC), U14.16 (VCC), U47.20 (VCC); also elsewhere on the board

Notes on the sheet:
COUNTERS
TRI-STATE BUFFER
CONNECTIONS
LEDs
POWER
When CE is HIGH, the counter will increment on each RISING_EDGE of the clock pulse. CARRY_OUT can be used to chain multiple counter modules together. JUMP, if set LOW, the counter will load the value asserted to the BUS pins. RESET, if set LOW, the counter will reset back to 0x00. OE, if set HIGH, 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
Smoothing Cap
5V+
